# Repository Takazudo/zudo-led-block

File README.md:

# Zudo LED Block

A narrow Eurorack art light that sits beside Kumiko blank panels: a clear cast-PMMA front with engraved, light-carrying letters and replaceable translucent PETG sides lit by eight individually addressable RGB LEDs. The active design is **A7**, alongside the immutable historical **Light Block A5** checkpoint and a Japanese documentation site.

Documentation (Japanese): https://zudo-led-block.zudolab.dev/ — **not live yet**; production hosting is configured but disabled until activated (see [hosting](doc/src/content/docs/project/hosting.mdx)).

> [!IMPORTANT]
> **A7 0.8 mm rigid FR-4 digital design integrated in PR #88 (3HP; transparent PET/FPC withdrawn; 2HP not adopted); not released for manufacture.** The current boards are controller `d83691d6…db2b` (0.8 mm, 4-layer JLC04081H-3313) and LED leaf `bcf2e35d…94cf9` (0.8 mm, 2-layer); the power adapter is the unchanged A5 board. The current file set is the review-only `engineering/a7/jlc-package/review/2026-11-22/` (REVIEW_ONLY / NOT FOR ORDER, named by `engineering/a7/jlc-package/package-sets.json`); `order/2026-11-13/` and its approvals belong to the old 1.6 mm / 0.6 mm boards and are not an upload choice. A prototype order still needs the owner's revision-specific route approval and the order-form checks; optical transmission and all physical qualification remain unmeasured.
>
> **Historical A5 is not released for manufacture.** The controller PCB is placed but **unrouted** (130 unconnected items, courtyard overlaps J3-H1 and J3-C7). Harness routing and installed fit are unresolved, and no physical electrical, optical, thermal, print or load qualification has happened. Passing CI is not an electronics or manufacturing approval.

**Historical A5 catalog status:** A5 design and BOM imported; all 30 fitted identities are migrated into the component-evidence catalog (`/docs/components/`), with explicit open gaps. The complete 30-type / 81-piece BOM is published on the site's [BOM page](doc/src/content/docs/architecture/bom.mdx) (generated from the A5 ledger and native netlists) and links each row to its catalog record. The reconciliation (30 identities / 71 placements / 81 pieces) is `provenance/a5-catalog/reconciliation.json`, built and checked by `scripts/a5_catalog.py`.

## A7 assembly preview

Run `pnpm dev`, then open `/docs/project/a7-preview/` (embedded) or `/a7-preview/` (standalone). For the built site: `pnpm build && pnpm --dir doc preview`. No live preview is claimed while hosting is disabled.

The viewer uses the existing GLBs with camera presets, orbit/pan/zoom, presentation-only explosion, visibility and named-part inspection. Sources and licences: [preview/a7/README.md](preview/a7/README.md). The [current A7 status](doc/src/content/docs/project/a7.mdx) and [next actions](doc/src/content/docs/project/next-actions.mdx) distinguish the new redesign, historical digital results and remaining physical work.

## Repository map

| Path | What it is |
| --- | --- |
| `engineering/a5/` | **Immutable** byte-for-byte import of the A5 checkpoint (786 files): native KiCad 10 projects, firmware + pinned STM32CubeG0 SDK and licenses, CadQuery generators, STEP/STL/3MF, front artwork, procurement ledger and evidence, historical verification records. Start with `engineering/a5/README_JA.md`, `continue-here.md`, `REPRODUCE.md`. |
| `provenance/` | Seed manifest (size + SHA-256 per file), original-archive recovery receipt, handoff evidence, and the five deliberately omitted paths ([provenance/README.md](provenance/README.md)). |
| `scripts/` | New tooling outside the checkpoint: seed verifier, A5 record checks, deterministic site-data generator, public-asset selection, browser checks, Cloudflare output check. |
| `doc/` | Documentation site (zudo-circuit-doc 0.3.0 on zudo-doc 9.1.3 / ZFB 5.2.2), Japanese-first. `doc/cloudflare.config.ts` + `doc/wrangler.config.ts` describe the (disabled) Workers Static Assets deployment. |
| `circuit/`, `circuit.config.ts`, `.claude/skills/` | zudo-circuit-doc project files; `circuit/WORKFLOW.md` is the canonical framework workflow. |
| `.github/workflows/` | Credential-free CI and the default-off production deploy gate. |

Agent instructions: [AGENTS.md](AGENTS.md) / [CLAUDE.md](CLAUDE.md).

## Setup and commands

Requirements: Node.js 24, pnpm 11.5.2 (`corepack enable`), Python ≥ 3.11 (standard library for the checks), GNU Make and a C11 compiler for firmware host tests, `arm-none-eabi-gcc` 13.2.1 for the ARM build.

```sh
pnpm install --frozen-lockfile

# A5 checkpoint integrity and data checks (no network, writes nothing in engineering/a5/)
pnpm a5:check                       # seed identity + record checks + generated-page drift
python3 engineering/a5/build_procurement_rows.py --check

# Firmware
make -C engineering/a5/firmware test test-sanitize timing
make -C engineering/a5/firmware arm  # needs arm-none-eabi-gcc on PATH

# Documentation
pnpm circuit:doctor
pnpm dev                            # local preview
pnpm build && pnpm check && pnpm check:site
pnpm test:browser                   # Playwright, desktop + mobile

# Cloudflare packaging (credential-free)
pnpm cf:build && pnpm cf:check-output && pnpm cf:dry-run
```

After an intentional change to the A5 inputs that feed the site (only by a new checkpoint import), run `pnpm a5:generate` and commit the regenerated pages.

## Reproduction paths beyond CI

| Area | Tooling | Notes |
| --- | --- | --- |
| Native electronics | KiCad 10.0.8 (`kicad-cli`, pcbnew Python) | CI runs the digest-pinned native gate, fresh schematic checks, the actual A7 controller candidate, negative controls and router reproduction. Imported A5 records remain historical. The framework's KiCad 9.0.9 preview renderer does not replace these native checks. |
| CAD | CadQuery 2.7.0, Python ≥ 3.11 (`engineering/a5/requirements.txt`) | `mechanical/build_mechanical.py --variant all` regenerates the four omitted tessellation JSONs before `render_previews.py`. |
| Workbook | `@oai/artifact-tool` + specialized runtime variables | Preserved as source; not a CI dependency. The PDF/XLSX in `engineering/a5/deliverables/` were **not** regenerated by this repository. |
| Full archive rebuild | `engineering/a5/build_package.py` | Requires restoring the five omitted files first. |

## License notes

Third-party material inside `engineering/a5/` keeps its own notices: STM32CubeG0 components (`engineering/a5/firmware/vendor/`, `firmware/dist/licenses/`), GCC runtime exception provenance, and upstream footprint licenses (`engineering/a5/electronics/footprints/upstream/LICENSE.md`).

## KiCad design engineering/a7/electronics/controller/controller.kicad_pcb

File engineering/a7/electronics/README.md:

# A7 コントローラー電子設計（R4, #19）

## 現行変更 #87（2026-11-17 JST）

controllerとLED leafを公称0.8 mm rigid FR-4へ変更しています。新leaf正本は `led_leaf/`、controller正本は `controller/`。両面maskは必要箇所以外を開口し、全銅層の広いGND面を撤去します。必要なGND returnは実配線と理由を記録した局所銅で成立させます。旧In1シールドを根拠にCV_FILTER/VLED干渉や電源returnを承認したことにはできず、最終配線・実stackup・Gerber・native gate・独立電気レビューを再確認します。現時点で新controllerのgraph/native検証完了を主張しません。

PET/FPCは撤回し、2HPの成立根拠が確保できないため0.8 mmの3HPを選びました。機能・MCU pin・CV伝達関数・modeを変えて成立扱いにはしません。A5は不変、A6は保留、旧注文・承認は旧identity専用です。最終結果は [#87](https://github.com/Takazudo/zudo-led-block/issues/87) とrevision付き証跡で確認してください。

## 変更前 revision 2 の履歴

以下の「現在」「PASS」「完了」、4層1.6 mm、In1 solid GNDと他層GND pour、CV_FILTERの面シールド評価はすべて変更前の記録です。新しい0.8 mm・広いGND面なしの設計には適用しません。

**状態: 回路図は独立電気レビュー済み（#24、head `1a2f31a`）。基板は配置・配線済み。初版はレイアウト・電気レビュー済み（PR #30、head `e2a2219`、main へのマージ `eb8adeb`、基板 sha256 `ec810aec…74f2`）。現在の基板はレビューの軽微な指摘 4 件を反映したリビジョン 2 で（基板 sha256 `4453f818…628e`）、PR #37 で独立した再レビューを通過しました（レビュー 5818812844、head `ae5aa3c`、ブロッキングなし。`eb5d833` での変更要求レビュー 5818789798 を解消）。main へのマージは `edf98c2` です。2026-11-12（#77）に SW1 の部品欄（MPN / LCSC）だけを HX MSK13C02 / C5149819 に変え、基板 sha256 は `89310d53…e727` になりました（フットプリント・銅・配置は同じ）。** 権威ある A7 基板 `controller/controller.kicad_pcb` を `candidate` とする A7 リビジョンゲート（`engineering/a7/verification/native_gate.json`）は新規実行で `PASS` です。これはデジタル検証だけの結果で、物理評価・製造リリースではありません。

## 何が A5 から変わったか

`scripts/a7_electronics.py` は不変の A5 設計データ（`engineering/a5/electronics/design/design_data.py`）を読み取り専用で読み込み、次の 3 部品だけを差し替えます。他の 69 部品・全ネットは A5 のままです。

| Ref | A5 | A7 | ピン → ネット |
| --- | --- | --- | --- |
| J1 (CV IN) | PJ-3582-B (C500090) | SOFNG PJ-324M (C22355739) | 1 SLEEVE→GND, 2 RING→GND, 3 RING normal→NC, 4 TIP→CV_THRU, 5 TIP normal→NC |
| J2 (CV THRU) | 同上 | 同上 | 同上（J1.4 と J2.4 は同一 CV_THRU ネット） |
| SW1 (ON/PGM/CV) | 1MS3T1B1M2QES-5 (C908270) | hanxia HX MSK13C02 (C5149819)。2026-11-12 に C&K PCM13SMTR (C221842、JLC 在庫 0) から変更、ランドは PCM13SMTR 用のまま | 3 COMMON→GND, 1→MODE_A, 4→MODE_B, 2→NC |

モード符号は不変です: POS.1 (1-3) で MODE_A=0,B=1 → ON、POS.2 (2-3, 端子 2 は未接続) で 1,1 → PROGRAM、POS.3 (3-4) で 1,0 → CV。0,0 には到達しません。R9/R10 のプルアップ、MCU ピン、CV 経路（C13→R7→U7、R24/R25、VADC=(100/133)*(VDD/2+CV/8)）、LED 左右ストリーム、電源ケーブルの極性は A5 と同一です（差分チェックで他の接続変化はゼロ）。

## 2026-11-09 の出典更新

PCM Series のメーカー一次資料 VL 03/14/25 を取得し、接点表とランド寸法は保持ミラーと一致しました。本体センタリング・実装適合は未確認です。PJ-324M C22355739 の実 supplier CAD も検査しましたが、symbol の端子 4/5 は現在の推定 tip/normal と不一致に見えます。穴寸法も異なります。これをメーカー証明として扱わず、導通・適合ゲートを維持し、基板は変更していません。詳細は各 owner bundle と `open-questions.md`。

## 元の設計入力と未確認事項（2026-11-08）

- **PJ-324M のピン機能は INFERRED**（R1 `pinmap-a7-pj-324m`）。メーカーのピン機能表はありません。入荷部品の導通試験（tip/ring/sleeve/normal をピンごと）が物理ゲートとして残ります。
- **PJ-324M の端子位置は MIRROR**（LCSC 掲載の SOFNG 図面）。across 方向の符号は部品面に対して未確認。**穴径は ASSUMED**（図面の向きに合わせた長穴: 1.6×0.8 mm ドリル、2.3×1.5 mm パッド。1 と 4 は軸に直交、2・3・5 は軸方向。1.2×0.40 mm ブレードに片側約 0.2 mm。図面に穴寸法なし、Q3）。軸から 5.4 mm の辺はピン 4/5 側、6.1 mm はピン 2/3 側（図面）。バレル突出は 3.5 mm。軸高さ約 3.0 mm は推定値のままで、確定寸法に昇格させていません。
- **PCM13SMTR のランドパターンは MIRROR**（C&K 文書の LCSC ミラー, sha256 `1c2ca483…`）。#24 の電気レビューの指摘で図面どおりに修正: 信号パッド 0.7×1.5 mm を x −3.0/−1.5/+1.5/+3.0（1.5/3.0/1.5 の寸法列、全幅 6.0）、ペグ線から 1.0〜2.5 mm。保持パッド 1.0×0.8 mm は内側スパン 9.3 mm・間隔 1.13 mm。Ø0.9 mm のペグ穴 5.0 mm ピッチ。本体のペグ線に対する位置は ASSUMED。
- **SW1 に載せる部品は HX MSK13C02（C5149819）**。オーナーの方針（動けばよい・安く・在庫あり）で 2026-11-12 に変更しました。Hanxia の図面（JLC 配布、MIRROR）の接点図は A = 1-3、B = 2-3、C = 3-4（3 が共通）で、ネットの割り当ては変わりません。上のランドはそのままで、Hanxia の推奨ランドとの公称値の比較は `switch-land-fit.json`（`scripts/a7_switch_fit.py`）にあります。穴は一致、信号パッドはメーカーパッドの 90.6 % を覆い、保持パッドは 73.9 %。実物での適合は switch-fit で確認します。
- 寸法ごとの出典区分は `footprints/footprint_sources.json` にあります。

## ファイルと所有区分

`controller/controller.kicad_pcb` は **authoritative** な配線済み基板です。通常の生成処理は上書きしません。回路図・ライブラリ・フットプリント等は `scripts/a7_electronics.py generate` の **derived** 出力、配置 export は fresh native facts からの派生物、README は authored です。所有区分は `engineering/a7/verification/source_authority.json` に従います。派生物は手で編集せず、各 generator の `--check` で確認します。A5 の回路図ライタの移植は `reproduce-a5` で A5 回路図をバイト一致で再生成して証明しています。

- `controller/` — 回路図、シンボルライブラリ、プロジェクト、ライブラリテーブル。A5 フットプリントは `engineering/a5/electronics/footprints/LightBlock.pretty` を読み取り専用で参照します。
- `footprints/LightBlockA7.pretty/` — PJ324M と PCM13SMTR のみ。

## 検証（新規実行、ピン留め KiCad 10.0.8 イメージ）

`python3 scripts/a7_schematic_check.py --out <リポジトリ外の空ディレクトリ>` が実行します。結果は `engineering/a7/verification/schematic/` にあります。

- ERC: 0 件（全重大度）
- 回路図→PCB パリティ: 0 件（`a7_electronics.py init-board` がリポジトリ外の空ディレクトリに生成した未配線のステージング基板に対して。ステージング基板の DRC/未接続数は基板結果ではありません）
- 振る舞いアサーション: 51 件すべて合格（レビュー記録済み）。差し替え部品（J1/J2/SW1）は全ピンが役割に割り当てられていること、未使用ピンがネットリストに実在することも確認します
- 承認差分チェック: 合格。観測差分 12 件（J1/J2/SW1 のフィールド）すべて component_replaced エントリでカバー。他部品の接続変化はゼロ

状態は `SCHEMATIC_REVIEWED` です。これは回路図フェーズの結果であり、基板・配線・物理ゲートの承認ではありません。レビュー記録（`authorized_delta.json` / `interface_roles/a7_controller.json` の `review`）は未解決の物理ゲートを列挙しています: PJ-324M のピン機能（TS/TRS 導通試験）、across 方向の符号、穴寸法（Q3）、軸高さ（Q1）、PCM13SMTR の本体センタリング、在庫（Q10）。

## 旧基板（配置・配線、revision 2）

- **外形と座標**: R2 の外形 16.2×62.9 mm、board_x = 組立 Z − 0.2、board_y = 組立 Y − 48.5。F 面が部品面、B 面ははんだ面で 0.6 mm の低背領域（R0603 とテストパッドだけ）。
- **層構成**: 4 層 1.6 mm。In1.Cu は GND のベタ、F・In2・B にも GND の塗りつぶし。信号層は F・In2・B。
- **配置**: `scripts/a7_board.py place` が R2 の `placement-envelopes.json` のキープアウトに対して配置を検査し、`controller/placement.json` に書きます。J1/J2/J3/J5/SW1 は R2 が決めた位置に固定（J3 は MP パッドの基板端クリアランスのため x 12.6）。
- **配線**: `scripts/a7_board.py build` がリポジトリ外の空ディレクトリに未配線の基板とパッド形状を作り、`scripts/a7_route.py`（0.1 mm 格子の negotiated-congestion ルーター、seed 0）が配線案を作り、`a7_board.py apply` が配線・ビア・GND の塗りつぶしを加えて充填します。結果を確認してから権威基板にコピーしました。配線案は `engineering/a7/verification/routing/route_proposal_seed0.json` に記録し、現在の配置から同じ結果が再現します。通常の再生成は権威基板を書きません。
- **設計ルール差分**: ビアを 0.6/0.3 mm から 0.5/0.2 mm に変更（`min_via_diameter`、`min_through_hole_diameter`、ネットクラスのビア）。U1 周辺の配線を通すために必要でした。JLCPCB の公開能力（多層 0.15/0.25 mm 以上、推奨最小穴 0.2 mm）に基づき、`native_gate.json` の `design_rule_delta` に理由と証拠（`engineering/a7/verification/fab/jlcpcb_capabilities.json`、URL・取得ハッシュ・該当行）を記録しています。アニュラーリング 0.15 mm、配線幅・クリアランス・層数は A5 のままです。
- **厳しくする方向だけのカスタムルール**: `controller/controller.kicad_dru` の `a7_pth_to_track` は、スルーホールの穴から他ネットのトラックまで 0.35 mm 以上を要求します（JLCPCB の推奨値。最小は 0.28 mm。A5 の穴クリアランス 0.2 mm より厳しい）。`a7_electronics.py generate` が `native_gate.json` の `design_rule_delta.custom_rules` と同じ内容で書き、ゲートは内容が違えば失敗します。負の対照 `control_pth_to_track` が穴から 0.32 mm のトラックを 1 本足し、このルール名で検出されることを毎回確かめます。現在の基板の最小値は 0.386 mm です。
- **配置チェックの比較精度**: コートヤードの比較は KiCad の内部単位（1 nm）に丸めてから行います（`native_gate.json` の `placement`）。ちょうど接する配置は DRC と同じく可、1 nm 以上の重なりは違反です。必要な隙間は 0 mm のままで、緩めていません。
- **ゲート結果**（ピン留め KiCad 10.0.8、新規実行）: ERC 0、パリティ 0、DRC 0、未接続 0、ゾーン再充填が一致、再生成で基板が変わらない、配置エクスポート `controller/board_placement.json` が最新。負の対照（配線切断・誤接続・充填ずれ・PTH–トラック・タイムアウト・A5 期待失敗・合成対照）はすべて検出。変異基板の DRC は、元の基板と同じプロジェクトルールとカスタムルールで実行します。

## 旧revision 2でのレビューと物理作業の記録

1. （完了）リビジョン 2 の再レビュー。PR #37 で再レビュー済みで、`edf98c2` で main にマージしました。軽微な指摘 4 件の結果は次のとおりです。C11 は U6.5 から 1.53 mm（以前 5.8 mm）。U7.2 と C17.2 の GND ビアはそれぞれ 0.52 mm と 0.66 mm（以前 1.5〜2 mm）。+5 V の C15 (10 µF) は U4.1 から 1.8 mm（以前は最寄りが C2 の 4.1 mm）。CV_FILTER は全長が F.Cu にあり、VLED との間隔は同じ層で 3.65 mm です。VLED が In2/B で下を横切りますが、間に In1 の GND プレーンがあります。
2. 物理ゲート: PJ-324M のピン導通・穴寸法・軸高さの実測、HX MSK13C02 の位置ごとの導通とランド適合（Q10）。

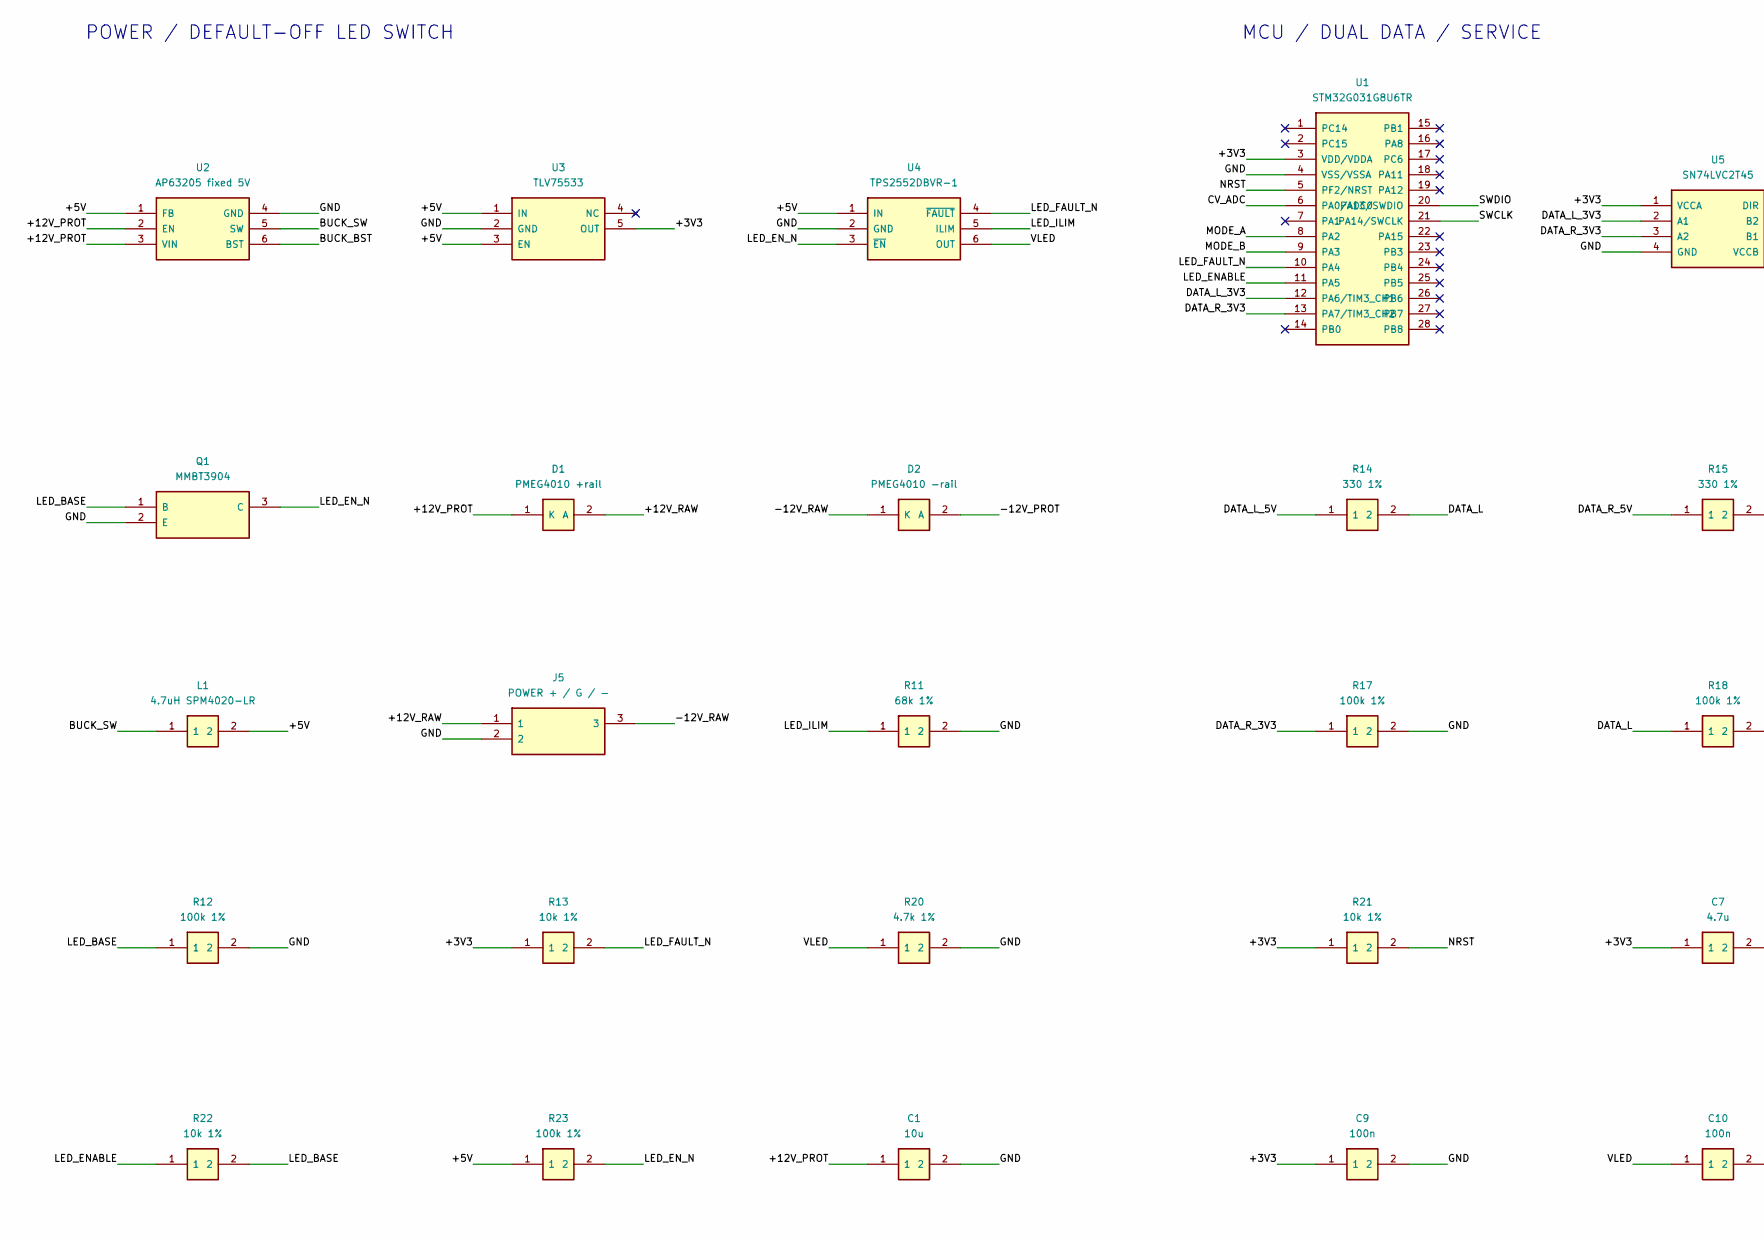
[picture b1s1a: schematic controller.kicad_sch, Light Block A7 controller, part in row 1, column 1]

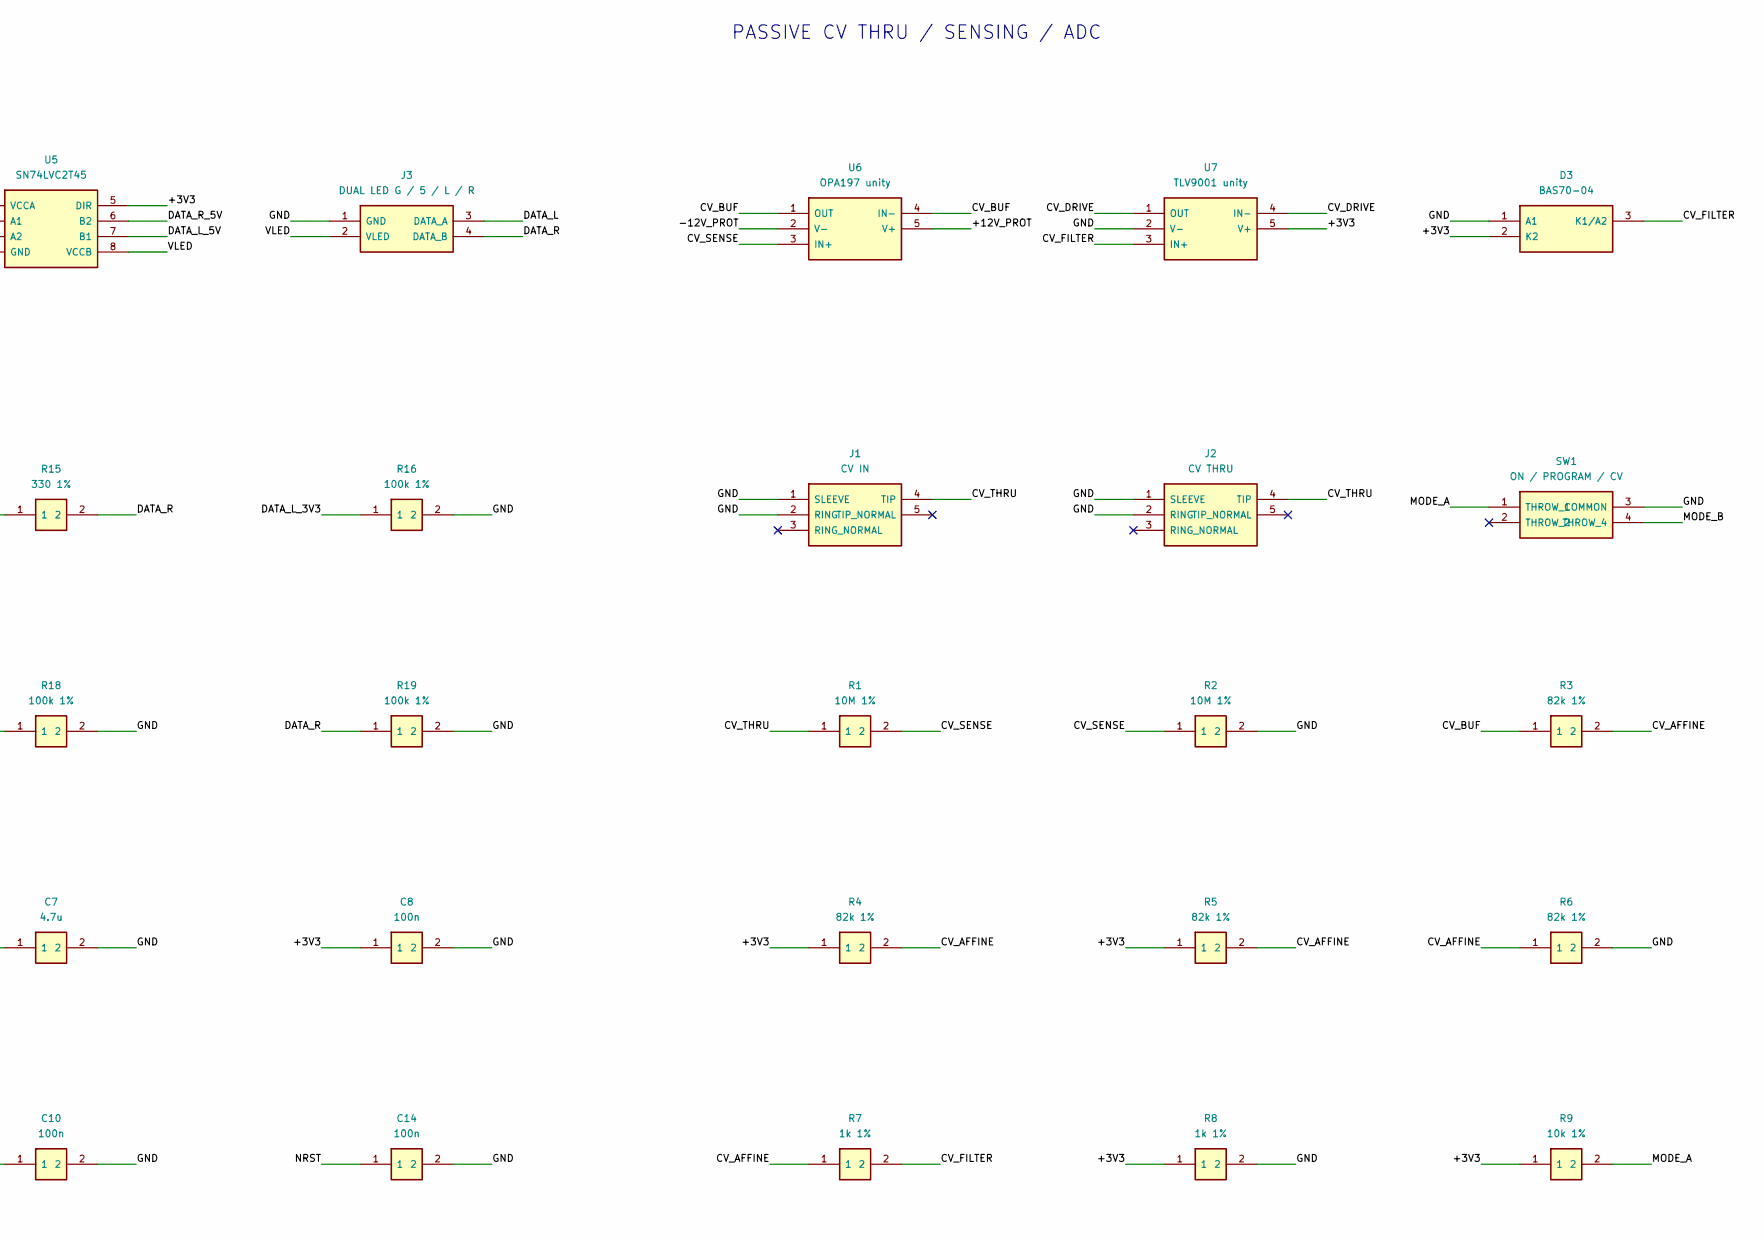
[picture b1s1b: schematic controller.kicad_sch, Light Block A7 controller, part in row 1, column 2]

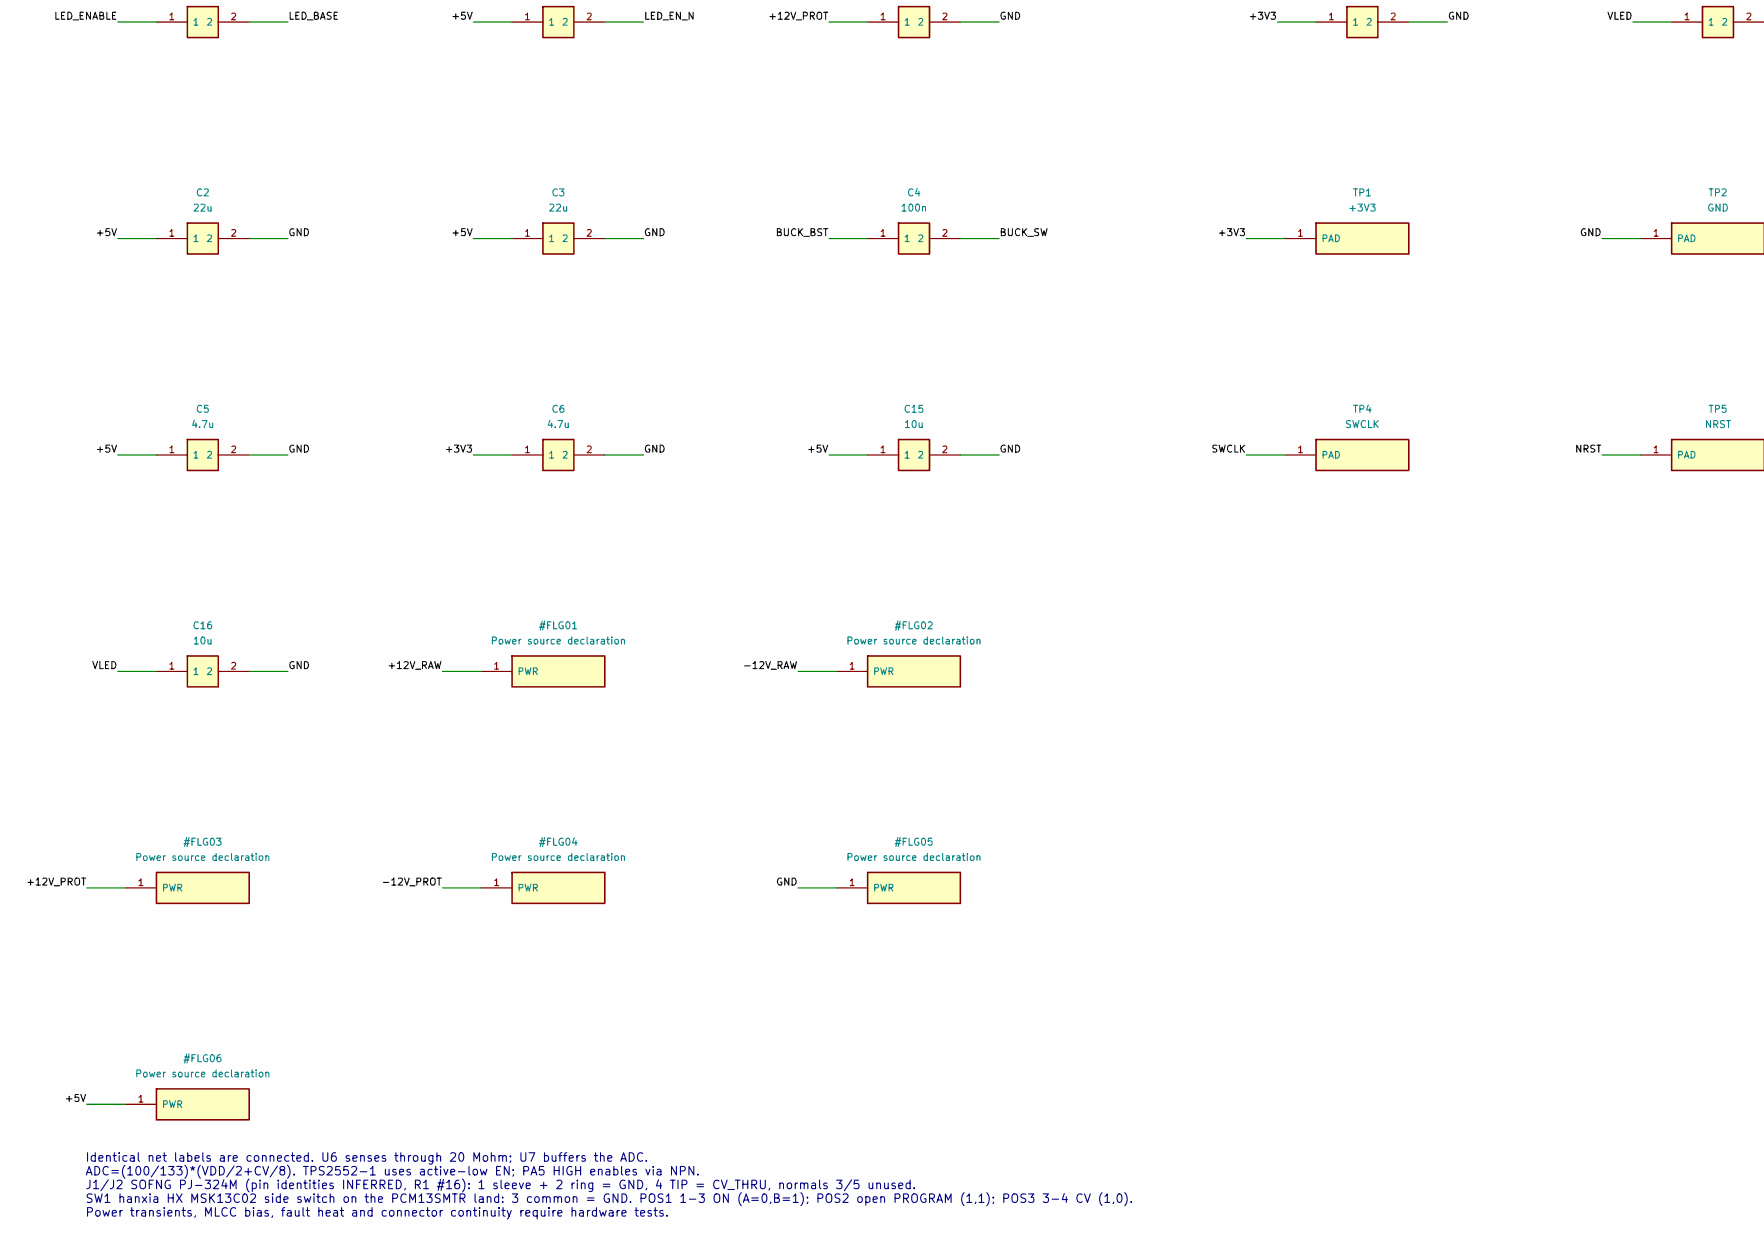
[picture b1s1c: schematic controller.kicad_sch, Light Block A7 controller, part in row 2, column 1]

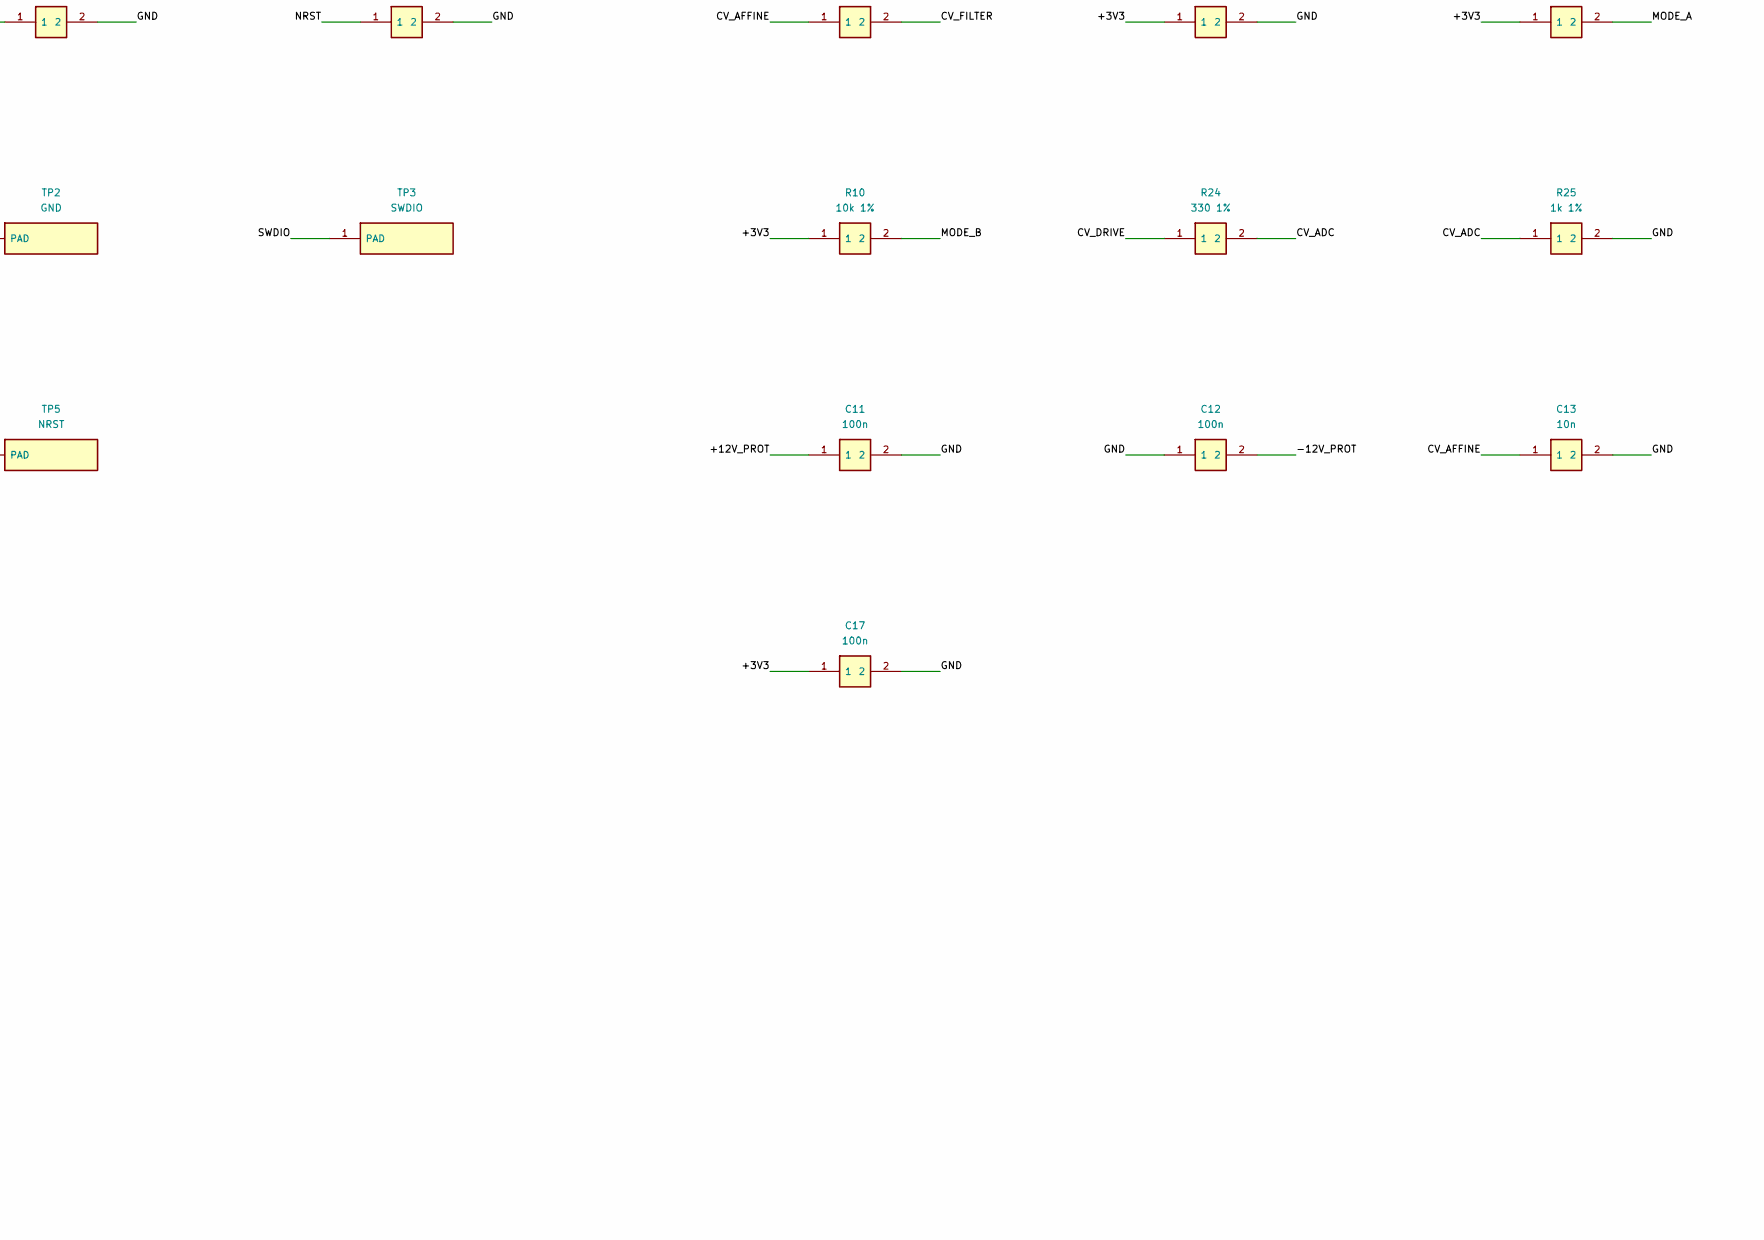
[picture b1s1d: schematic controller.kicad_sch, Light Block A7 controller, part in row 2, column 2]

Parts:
C1, C15, C16: 10u; C0805; MPN CL21A106KAYNNNE; LCSC C15850
C2, C3: 22u; C1206; MPN CL31A226KAHNNNE; LCSC C12891
C4, C8, C9, C10, C11, C12, C14, C17: 100n; C0603; MPN CC0603KRX7R9BB104; LCSC C14663
C5, C6, C7: 4.7u; C0603; MPN CL10A475KO8NNNC; LCSC C19666
C13: 10n; C0603; MPN 0603B103K500NT; LCSC C57112
D1: PMEG4010 +rail; SOD323F; MPN PMEG4010CEJ,115; LCSC C50704
D2: PMEG4010 -rail; SOD323F; MPN PMEG4010CEJ,115; LCSC C50704
D3: BAS70-04; SOT23; MPN BAS70-04-7-F; LCSC C134375
J1: CV IN; PJ324M; MPN PJ-324M; LCSC C22355739
J2: CV THRU; PJ324M; MPN PJ-324M; LCSC C22355739
J3: DUAL LED G / 5 / L / R; JST_SH4; MPN SM04B-SRSS-TB(LF)(SN); LCSC C160404
J5: POWER + / G / -; PICO3; MPN 530470310; LCSC C122442
L1: 4.7uH SPM4020-LR; SPM4020_LR; MPN SPM4020T-4R7M-LR; LCSC C694586
Q1: MMBT3904; SOT23; MPN MMBT3904(RANGE:100-300); LCSC C20526
R1, R2: 10M 1%; R0603; MPN 0603WAF1005T5E; LCSC C7250
R3, R4, R5, R6: 82k 1%; R0603; MPN 0603WAF8202T5E; LCSC C23254
R7, R8, R25: 1k 1%; R0603; MPN 0603WAF1001T5E; LCSC C21190
R9, R10, R13, R21, R22: 10k 1%; R0603; MPN 0603WAF1002T5E; LCSC C25804
R11: 68k 1%; R0603; MPN 0603WAF6802T5E; LCSC C23231
R12, R16, R17, R18, R19, R23: 100k 1%; R0603; MPN 0603WAF1003T5E; LCSC C25803
R14, R15, R24: 330 1%; R0603; MPN 0603WAF3300T5E; LCSC C23138
R20: 4.7k 1%; R0603; MPN 0603WAF4701T5E; LCSC C23162
SW1: ON / PROGRAM / CV; PCM13SMTR; MPN HX MSK13C02; LCSC C5149819
TP1: +3V3; TESTPAD
TP2: GND; TESTPAD
TP3: SWDIO; TESTPAD
TP4: SWCLK; TESTPAD
TP5: NRST; TESTPAD
U1: STM32G031G8U6TR; QFN28; MPN STM32G031G8U6TR; LCSC C5270180
U2: AP63205 fixed 5V; TSOT26; MPN AP63205WU-7; LCSC C2071056
U3: TLV75533; DBV5; MPN TLV75533PDBVR; LCSC C404027
U4: TPS2552DBVR-1; DBV6; MPN TPS2552DBVR-1; LCSC C140331
U5: SN74LVC2T45; DCU8; MPN SN74LVC2T45DCUR; LCSC C15741
U6: OPA197 unity; DBV5; MPN OPA197IDBVR; LCSC C221351
U7: TLV9001 unity; DBV5; MPN TLV9001IDBVR; LCSC C398363

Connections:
/+3V3: C6.1, C7.1, C8.1, C9.1, C17.1, D3.2 (K2), R4.1, R5.1, R8.1, R9.1, R10.1, R13.1, R21.1, TP1.1, U1.3 (VDD/VDDA), U3.5 (OUT), U5.1 (VCCA), U5.5 (DIR), U7.5 (V+)
/+5V: C2.1, C3.1, C5.1, C15.1, L1.2, R23.1, U2.1 (FB), U3.1 (IN), U3.3 (EN), U4.1 (IN)
/+12V_PROT: C1.1, C11.1, D1.1 (K), U2.2 (EN), U2.3 (VIN), U6.5 (V+)
/+12V_RAW: D1.2 (A), J5.1
/-12V_PROT: C12.2, D2.2 (A), U6.2 (V-)
/-12V_RAW: D2.1 (K), J5.3
/BUCK_BST: C4.1, U2.6 (BST)
/BUCK_SW: C4.2, L1.1, U2.5 (SW)
/CV_ADC: R24.2, R25.1, U1.6 (PA0/ADC0)
/CV_AFFINE: C13.1, R3.2, R4.2, R5.2, R6.1, R7.1
/CV_BUF: R3.1, U6.1 (OUT), U6.4 (IN-)
/CV_DRIVE: R24.1, U7.1 (OUT), U7.4 (IN-)
/CV_FILTER: D3.3 (K1/A2), R7.2, U7.3 (IN+)
/CV_SENSE: R1.2, R2.1, U6.3 (IN+)
/CV_THRU: J1.4 (TIP), J2.4 (TIP), R1.1
/DATA_L: J3.3 (DATA_A), R14.2, R18.1
/DATA_L_3V3: R16.1, U1.12 (PA6/TIM3_CH1), U5.2 (A1)
/DATA_L_5V: R14.1, U5.7 (B1)
/DATA_R: J3.4 (DATA_B), R15.2, R19.1
/DATA_R_3V3: R17.1, U1.13 (PA7/TIM3_CH2), U5.3 (A2)
/DATA_R_5V: R15.1, U5.6 (B2)
/GND: C1.2, C2.2, C3.2, C5.2, C6.2, C7.2, C8.2, C9.2, C10.2, C11.2, C12.1, C13.2, C14.2, C15.2, C16.2, C17.2, D3.1 (A1), J1.1 (SLEEVE), J1.2 (RING), J2.1 (SLEEVE), J2.2 (RING), J3.1 (GND), J5.2, Q1.2 (E), R2.2, R6.2, R8.2, R11.2, R12.2, R16.2, R17.2, R18.2, R19.2, R20.2, R25.2, SW1.3 (COMMON), TP2.1, U1.4 (VSS/VSSA), U2.4 (GND), U3.2 (GND), U4.2 (GND), U5.4 (GND), U7.2 (V-)
/LED_BASE: Q1.1 (B), R12.1, R22.2
/LED_ENABLE: R22.1, U1.11 (PA5)
/LED_EN_N: Q1.3 (C), R23.2, U4.3 (~EN)
/LED_FAULT_N: R13.2, U1.10 (PA4), U4.4 (~FAULT)
/LED_ILIM: R11.1, U4.5 (ILIM)
/MODE_A: R9.2, SW1.1 (THROW_1), U1.8 (PA2)
/MODE_B: R10.2, SW1.4 (THROW_4), U1.9 (PA3)
/NRST: C14.1, R21.2, TP5.1, U1.5 (PF2/NRST)
/SWCLK: TP4.1, U1.21 (PA14/SWCLK)
/SWDIO: TP3.1, U1.20 (PA13/SWDIO)
/VLED: C10.1, C16.1, J3.2 (VLED), R20.1, U4.6 (OUT), U5.8 (VCCB)

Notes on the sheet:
POWER / DEFAULT-OFF LED SWITCH
MCU / DUAL DATA / SERVICE
PASSIVE CV THRU / SENSING / ADC
Identical net labels are connected. U6 senses through 20 Mohm; U7 buffers the ADC. ADC=(100/133)*(VDD/2+CV/8). TPS2552-1 uses active-low EN; PA5 HIGH enables via NPN. J1/J2 SOFNG PJ-324M (pin identities INFERRED, R1 #16): 1 sleeve + 2 ring = GND, 4 TIP = CV_THRU, normals 3/5 unused. SW1 hanxia HX M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

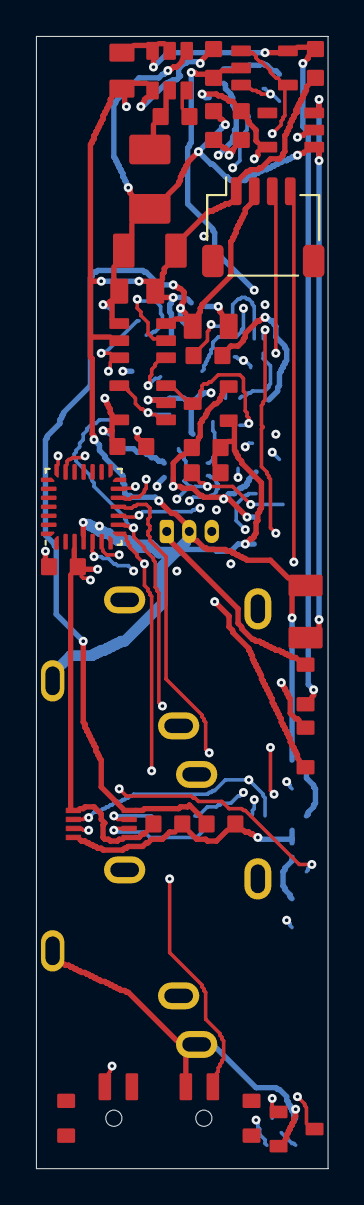
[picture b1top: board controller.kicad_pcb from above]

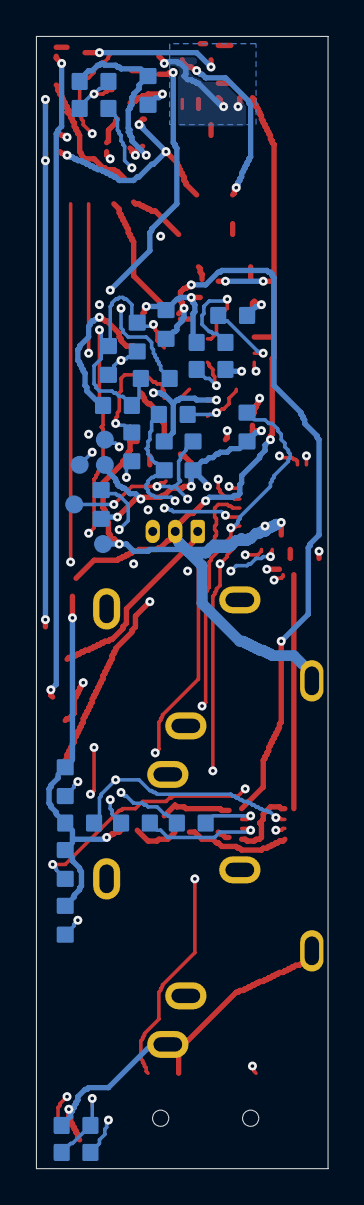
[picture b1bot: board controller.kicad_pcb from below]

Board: 4 copper layers, 16.2 x 62.9 mm, 64 parts (30 on the bottom side), 33 nets.

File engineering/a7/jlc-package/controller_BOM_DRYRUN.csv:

Comment,Designator,Footprint,JLCPCB Part #
10u,"C1,C15,C16",C0805,C15850
22u,"C2,C3",C1206,C12891
100n,"C4,C8,C9,C10,C11,C12,C14,C17",C0603,C14663
4.7u,"C5,C6,C7",C0603,C19666
10n,C13,C0603,C57112
PMEG4010 +rail,"D1,D2",SOD323F,C50704
BAS70-04,D3,SOT23,C134375
CV IN,"J1,J2",PJ324M,C22355739
DUAL LED G / 5 / L / R,J3,JST_SH4,C160404
POWER + / G / -,J5,PICO3,C122442
4.7uH SPM4020-LR,L1,SPM4020_LR,C694586
MMBT3904,Q1,SOT23,C20526
10M 1%,"R1,R2",R0603,C7250
82k 1%,"R3,R4,R5,R6",R0603,C23254
1k 1%,"R7,R8,R25",R0603,C21190
10k 1%,"R9,R10,R13,R21,R22",R0603,C25804
68k 1%,R11,R0603,C23231
100k 1%,"R12,R16,R17,R18,R19,R23",R0603,C25803
330 1%,"R14,R15,R24",R0603,C23138
4.7k 1%,R20,R0603,C23162
ON / PROGRAM / CV,SW1,PCM13SMTR,C221842
STM32G031G8U6TR,U1,QFN28,C5270180
AP63205 fixed 5V,U2,TSOT26,C2071056
TLV75533,U3,DBV5,C404027
TPS2552DBVR-1,U4,DBV6,C140331
SN74LVC2T45,U5,DCU8,C15741
OPA197 unity,U6,DBV5,C221351
TLV9001 unity,U7,DBV5,C398363

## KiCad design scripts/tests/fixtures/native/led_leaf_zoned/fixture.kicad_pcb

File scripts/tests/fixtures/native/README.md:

# Native gate infrastructure fixtures

Test infrastructure for `scripts/native_gate/`. **Not an A7 board, not an A5 revision, not a manufacturing file.**

- `led_leaf_zoned/` — the immutable A5 LED leaf's routing plus one filled GND zone on F.Cu, built by
  `scripts/native_gate/make_fixture.py` inside the pinned KiCad 10.0.8 image into an empty directory, then committed.
  `provenance.json` records the A5 source hashes and outputs. Regeneration is not byte-identical (KiCad assigns new
  UUIDs), so the committed board is the fixture authority and `profile.lock.json` pins it.
- `led_leaf_zoned/placement.json` — derived by `authority.py export-placement` from fresh native facts; the gate
  re-checks it as its regeneration-preservation step.
- `profile.json` / `profile.lock.json` — the infrastructure gate profile and its generated input lock.
- `a5_identity_delta.json` — identity record: a fresh export of the A5 controller schematic must equal the
  historical A5 netlist with no delta.

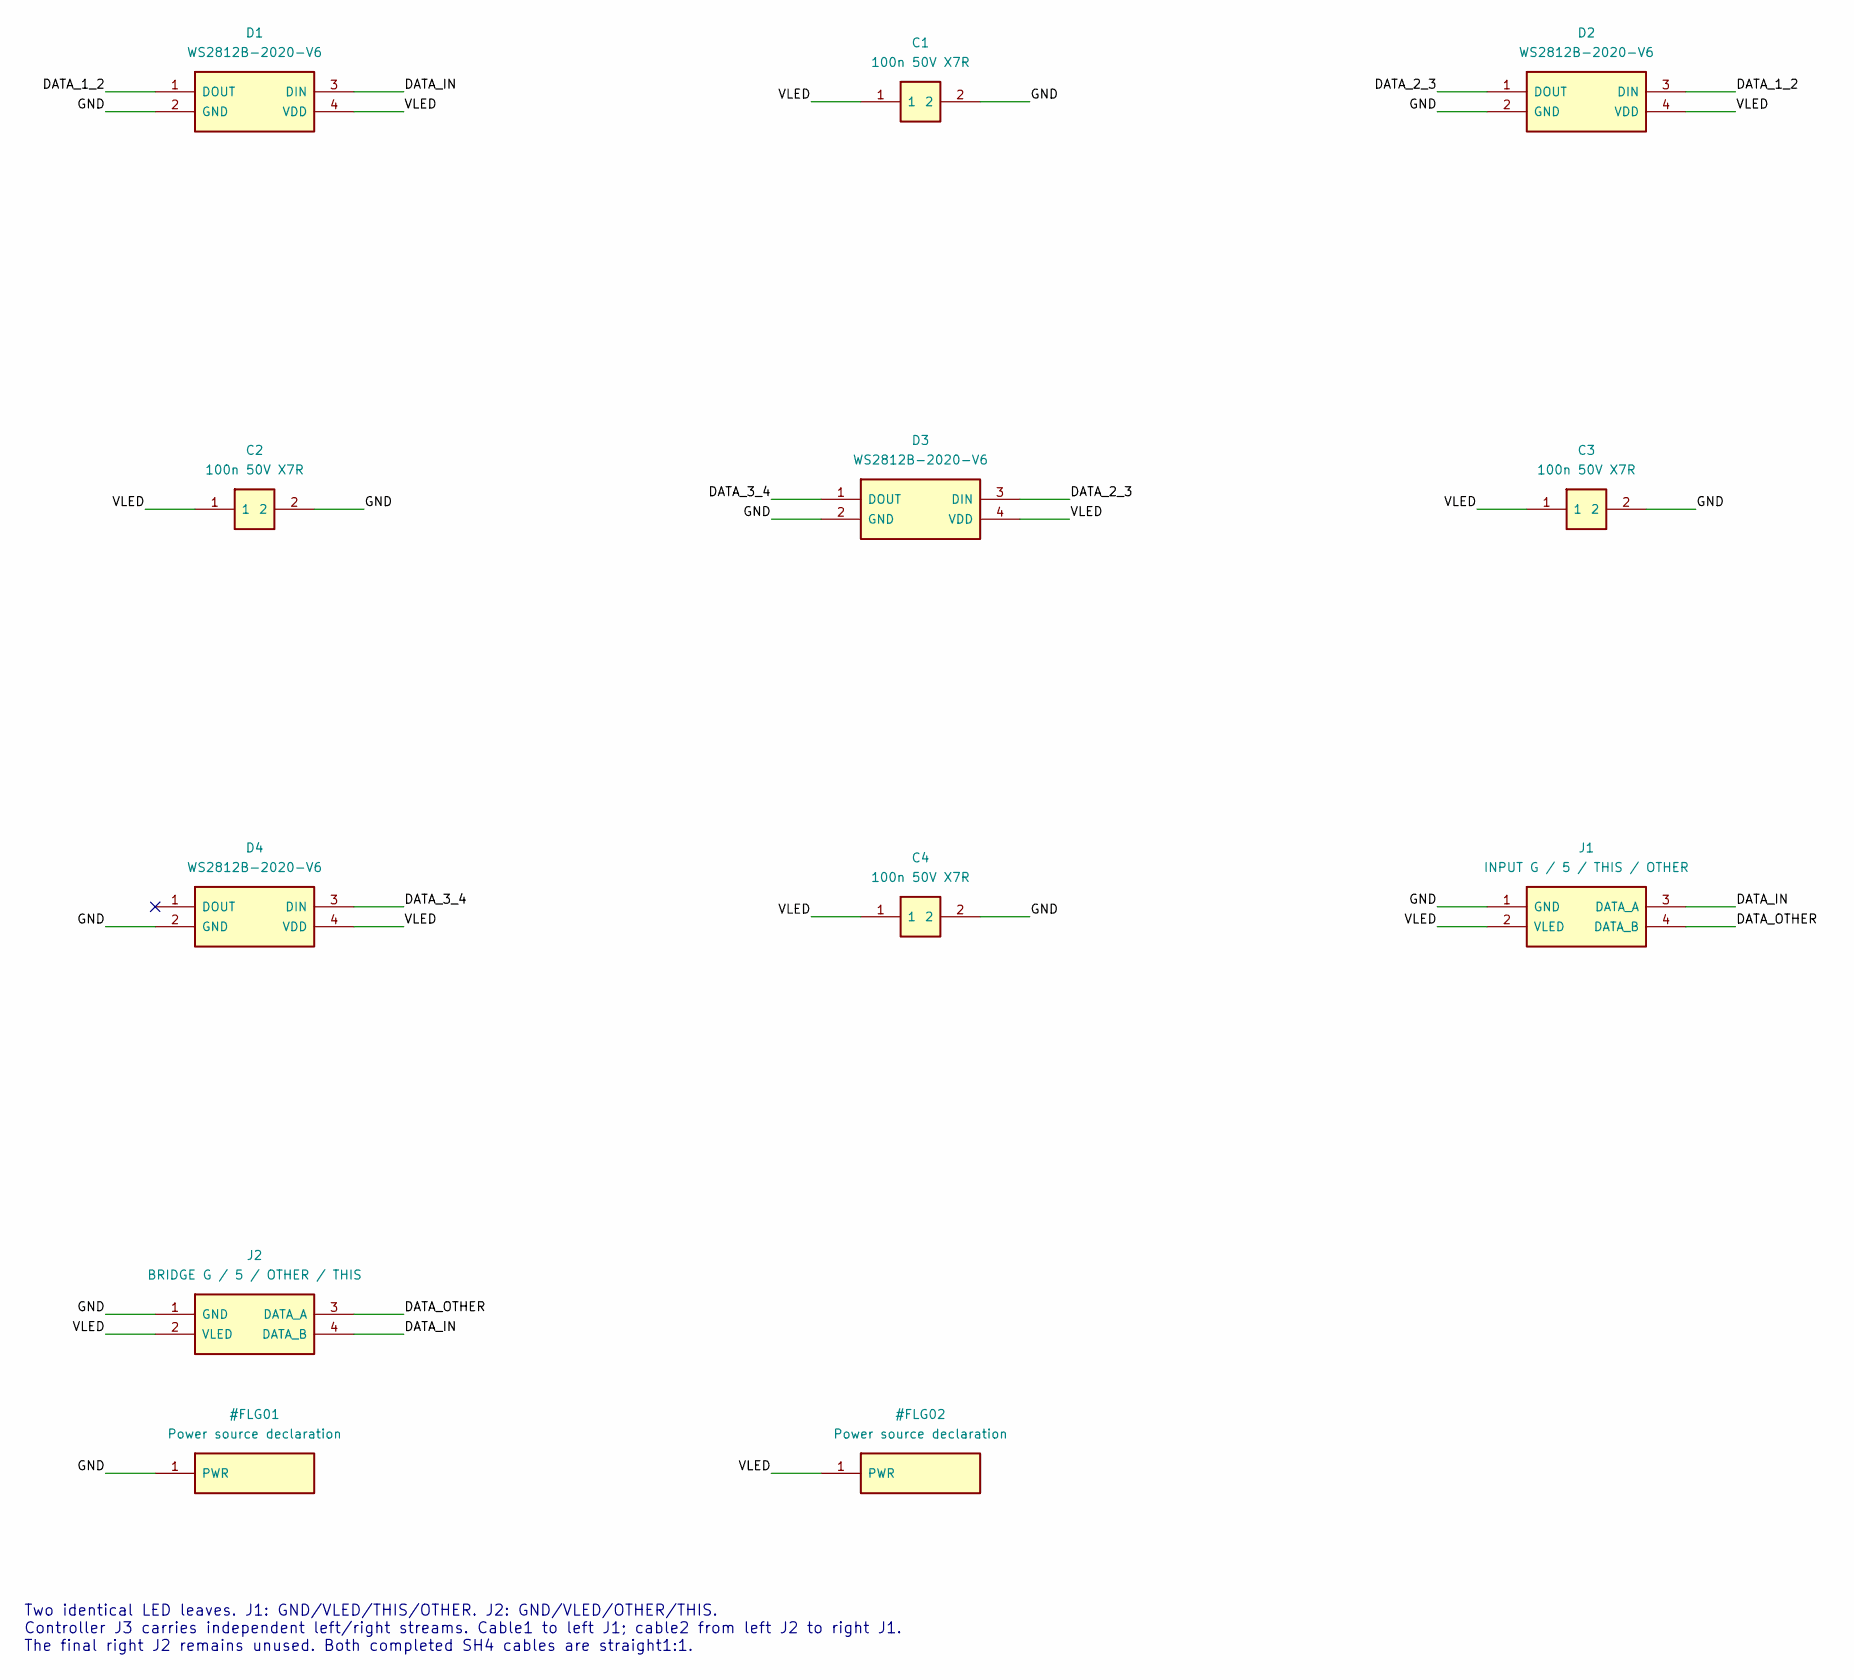
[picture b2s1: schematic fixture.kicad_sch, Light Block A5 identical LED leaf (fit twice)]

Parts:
C1, C2, C3, C4: 100n 50V X7R; C0603; MPN CC0603KRX7R9BB104; LCSC C14663
D1, D2, D3, D4: WS2812B-2020-V6; WS2812B_2020_V6; MPN WS2812B-2020-V6; LCSC C52917434
J1: INPUT G / 5 / THIS / OTHER; JST_SH4; MPN SM04B-SRSS-TB(LF)(SN); LCSC C160404
J2: BRIDGE G / 5 / OTHER / THIS; JST_SH4; MPN SM04B-SRSS-TB(LF)(SN); LCSC C160404

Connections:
DATA_1_2: D1.1 (DOUT), D2.3 (DIN)
DATA_2_3: D2.1 (DOUT), D3.3 (DIN)
DATA_3_4: D3.1 (DOUT), D4.3 (DIN)
DATA_IN: D1.3 (DIN), J1.3 (DATA_A), J2.4 (DATA_B)
DATA_OTHER: J1.4 (DATA_B), J2.3 (DATA_A)
GND: C1.2, C2.2, C3.2, C4.2, D1.2 (GND), D2.2 (GND), D3.2 (GND), D4.2 (GND), J1.1 (GND), J2.1 (GND)
VLED: C1.1, C2.1, C3.1, C4.1, D1.4 (VDD), D2.4 (VDD), D3.4 (VDD), D4.4 (VDD), J1.2 (VLED), J2.2 (VLED)

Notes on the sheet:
Two identical LED leaves. J1: GND/VLED/THIS/OTHER. J2: GND/VLED/OTHER/THIS. Controller J3 carries independent left/right streams. Cable1 to left J1; cable2 from left J2 to right J1. The final right J2 remains unused. Both completed SH4 cables are straight1:1.

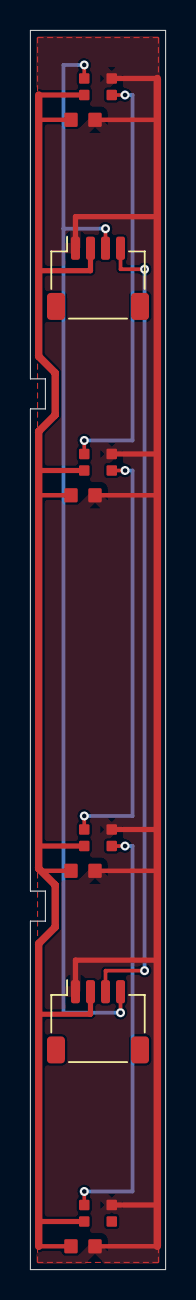
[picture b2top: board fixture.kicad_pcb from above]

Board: 2 copper layers, 9.0 x 82.5 mm, 10 parts (0 on the bottom side), 7 nets.
